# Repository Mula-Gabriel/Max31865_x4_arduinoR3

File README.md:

Fichier format kicad v6.
Shield pour 4 sondes pt100 3/4 fils, format arduino, avec 4 max31865.

# Max31865_x4_arduinoR3   
Exemple code https://github.com/Mula-Gabriel/Max31865_x4_arduinoR3_STM32

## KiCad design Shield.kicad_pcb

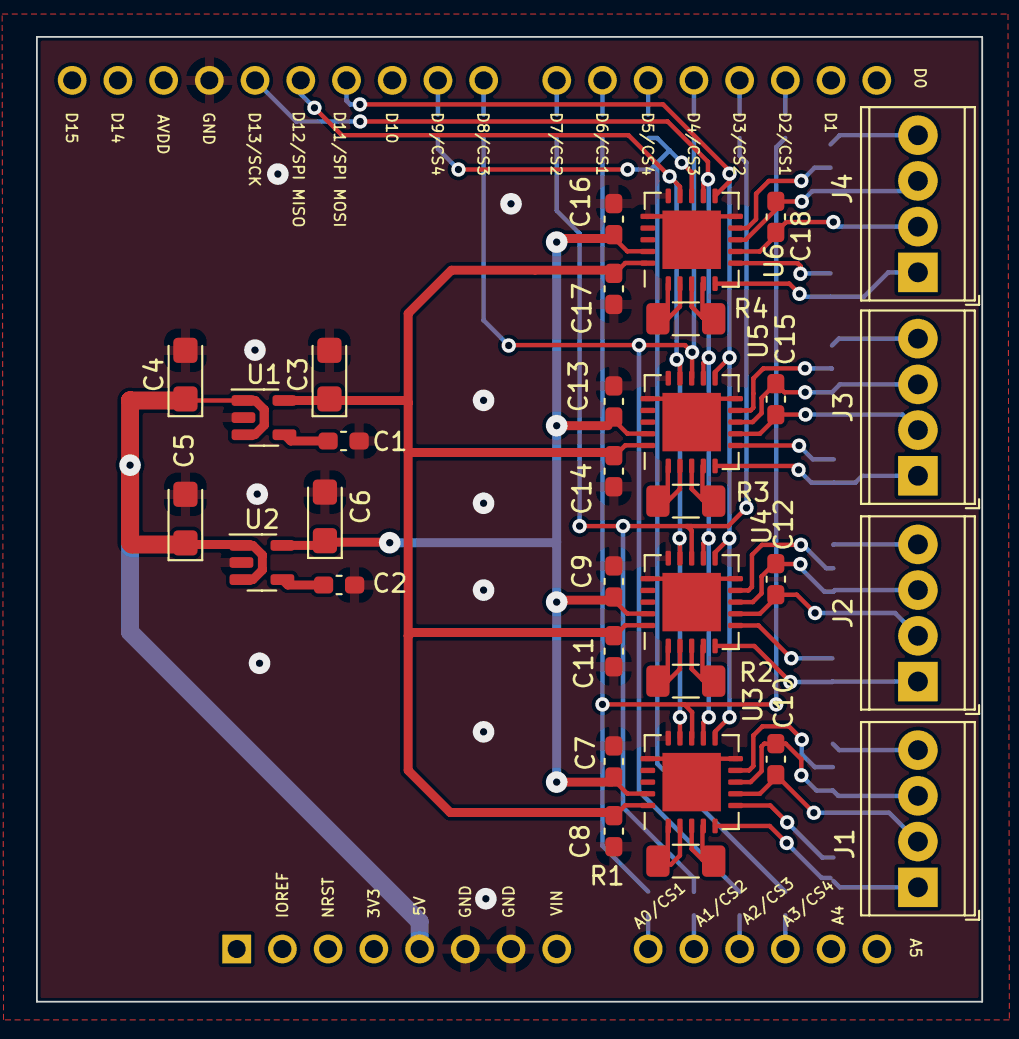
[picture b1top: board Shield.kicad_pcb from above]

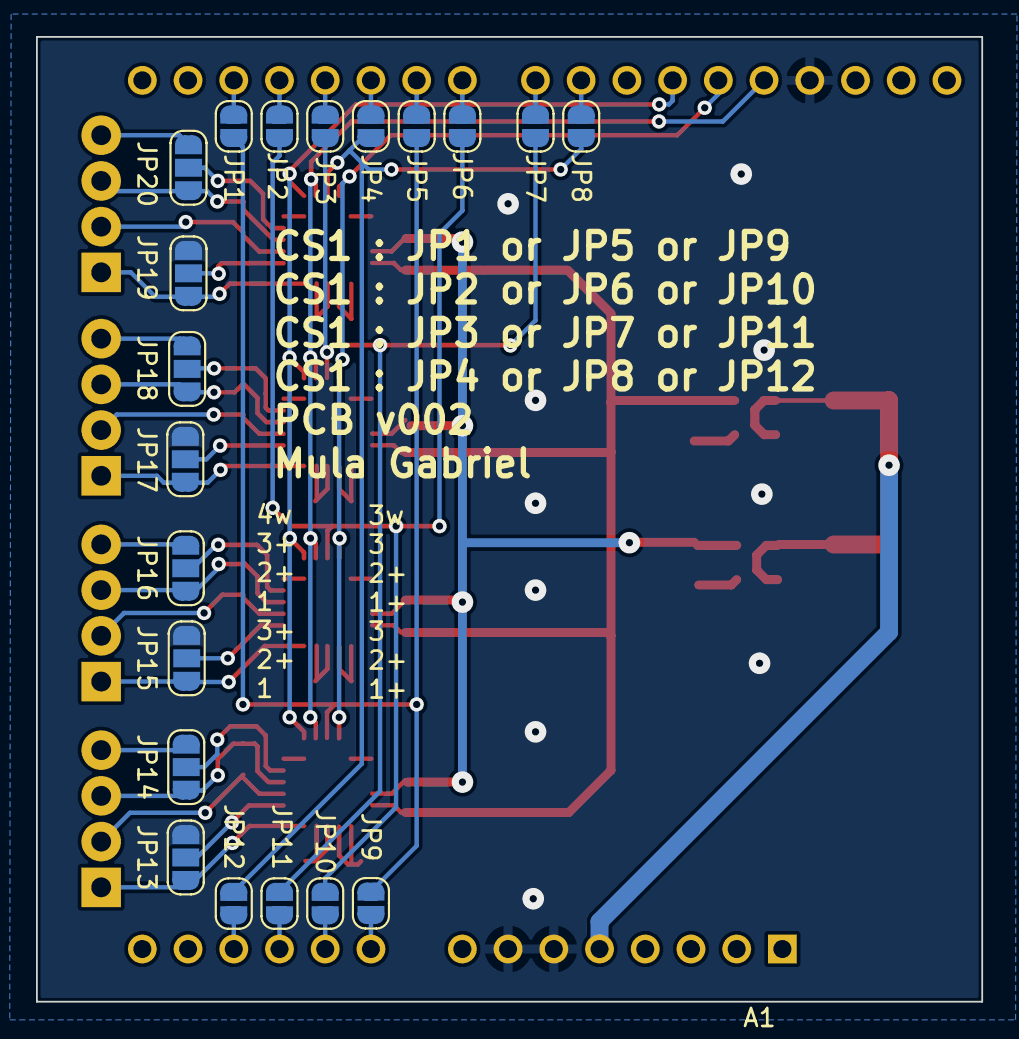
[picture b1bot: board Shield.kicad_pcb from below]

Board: 2 copper layers, 52.5 x 53.6 mm, 53 parts (21 on the bottom side), 57 nets.

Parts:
A1: Arduino_UNO_R3; Arduino_UNO_R3_3d
C1, C2: 100 nF; C_0603_1608Metric_Pad1.08x0.95mm_HandSolder
C3, C6: 10uF; CP_EIA-3216-18_Kemet-A
C4, C5: 1uF; CP_EIA-3216-18_Kemet-A
C7, C8, C9, C10, C11, C12, C13, C14, C15, C16, C17, C18: 100nF; C_0603_1608Metric_Pad1.08x0.95mm_HandSolder
J1, J2, J3, J4: Screw_Terminal_01x04; TerminalBlock_Phoenix_MPT-0,5-4-2.54_1x04_P2.54mm_Horizontal
JP1, JP2, JP3, JP4, JP5, JP6, JP7, JP8: SolderJumper_2_Open; SolderJumper-2_P1.3mm_Open_RoundedPad1.0x1.5mm
JP9, JP10, JP11, JP12: SolderJumper_2_Bridged; SolderJumper-2_P1.3mm_Open_RoundedPad1.0x1.5mm
JP13, JP14, JP15, JP16, JP17, JP18, JP19, JP20: SolderJumper_3_Open; SolderJumper-3_P1.3mm_Open_RoundedPad1.0x1.5mm_NumberLabels
R1, R2, R3, R4: 400 0.1%; R_1206_3216Metric_Pad1.30x1.75mm_HandSolder
U1, U2: SPX3819M5-L-3-3; SOT-23-5
U3, U4, U5, U6: MAX31865xTP; TQFN-20-1EP_5x5mm_P0.65mm_EP3.25x3.25mm

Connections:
+3.3V: C6.1, C7.2, C9.2, C13.2, C16.2, U2.5 (OUT), U3.19 (DVDD), U4.19 (DVDD), U5.19 (DVDD), U6.19 (DVDD)
+3.3VA: C3.1, C8.1, C11.1, C14.1, C17.1, U1.5 (OUT), U3.20 (VDD), U4.20 (VDD), U5.20 (VDD), U6.20 (VDD)
+5V: A1.5 (+5V), C4.1, C5.1, U1.1 (IN), U1.3 (EN), U2.1 (IN), U2.3 (EN)
/CS_MAX1: JP1.1 (A), JP5.1 (A), JP9.2 (B), U3.13 (~CS)
/CS_MAX2: JP2.1 (A), JP6.1 (A), JP10.2 (B), U4.13 (~CS)
/CS_MAX3: JP3.1 (A), JP7.1 (A), JP11.2 (B), U5.13 (~CS)
/CS_MAX4: JP4.1 (A), JP8.1 (A), JP12.2 (B), U6.13 (~CS)
/SPI2_MISO: A1.27 (D12), U3.14 (SDO), U4.14 (SDO), U5.14 (SDO), U6.14 (SDO)
/SPI2_MOSI: A1.26 (D11), U3.11 (SDI), U4.11 (SDI), U5.11 (SDI), U6.11 (SDI)
/SPI2_SCK: A1.28 (D13), U3.12 (SCLK), U4.12 (SCLK), U5.12 (SCLK), U6.12 (SCLK)
GND: A1.6 (GND), A1.7 (GND), A1.29 (GND), C1.2, C2.2, C3.2, C4.2, C5.2, C6.2, C7.1, C8.2, C9.1, C11.2, C13.1, C14.2, C16.1, C17.2, JP13.3 (B), JP15.3 (B), JP17.3 (B), JP19.3 (B), U1.2 (GND), U2.2 (GND), U3.10 (GND), U3.15 (DGND), U3.16 (GND), U3.21 (GND), U4.10 (GND), U4.15 (DGND), U4.16 (GND), U4.21 (GND), U5.10 (GND), U5.15 (DGND), U5.16 (GND), U5.21 (GND), U6.10 (GND), U6.15 (DGND), U6.16 (GND), U6.21 (GND)
unnamed: A1.9 (A0), JP9.1 (A)
unnamed: A1.10 (A1), JP10.1 (A)
unnamed: A1.11 (A2), JP11.1 (A)
unnamed: A1.12 (A3), JP12.1 (A)
unnamed: A1.17 (D2), JP1.2 (B)
unnamed: A1.18 (D3), JP2.2 (B)
unnamed: A1.19 (D4), JP3.2 (B)
unnamed: A1.20 (D5), JP4.2 (B)
unnamed: A1.21 (D6), JP5.2 (B)
unnamed: A1.22 (D7), JP6.2 (B)
unnamed: A1.23 (D8), JP7.2 (B)
unnamed: A1.24 (D9), JP8.2 (B)
unnamed: C1.1, U1.4 (BP)
unnamed: C2.1, U2.4 (BP)
unnamed: C10.1, J1.3, JP14.1 (A), U3.8 (RTDIN-)
unnamed: C10.2, J1.2, U3.7 (RTDIN+)
unnamed: C12.1, J2.3, JP16.1 (A), U4.8 (RTDIN-)
unnamed: C12.2, J2.2, U4.7 (RTDIN+)
unnamed: C15.1, J3.3, JP18.1 (A), U5.8 (RTDIN-)
unnamed: C15.2, J3.2, U5.7 (RTDIN+)
unnamed: C18.1, J4.3, JP20.1 (A), U6.8 (RTDIN-)
unnamed: C18.2, J4.2, U6.7 (RTDIN+)
unnamed: J1.1, JP13.1 (A), U3.5 (FORCE+)
unnamed: J1.4, JP14.3 (B)
unnamed: J2.1, JP15.1 (A), U4.5 (FORCE+)
unnamed: J2.4, JP16.3 (B)
unnamed: J3.1, JP17.1 (A), U5.5 (FORCE+)
unnamed: J3.4, JP18.3 (B)
unnamed: J4.1, JP19.1 (A), U6.5 (FORCE+)
unnamed: J4.4, JP20.3 (B)
unnamed: JP13.2 (C), U3.6 (FORCE2)
unnamed: JP14.2 (C), U3.9 (FORCE-)
unnamed: JP15.2 (C), U4.6 (FORCE2)
unnamed: JP16.2 (C), U4.9 (FORCE-)
unnamed: JP17.2 (C), U5.6 (FORCE2)
unnamed: JP18.2 (C), U5.9 (FORCE-)
unnamed: JP19.2 (C), U6.6 (FORCE2)
unnamed: JP20.2 (C), U6.9 (FORCE-)
unnamed: R1.1, U3.1 (BIAS), U3.2 (REFIN+)
unnamed: R1.2, U3.3 (REFIN-), U3.4 (ISENSOR)
unnamed: R2.1, U4.1 (BIAS), U4.2 (REFIN+)
unnamed: R2.2, U4.3 (REFIN-), U4.4 (ISENSOR)
unnamed: R3.1, U5.1 (BIAS), U5.2 (REFIN+)
unnamed: R3.2, U5.3 (REFIN-), U5.4 (ISENSOR)
unnamed: R4.1, U6.1 (BIAS), U6.2 (REFIN+)
unnamed: R4.2, U6.3 (REFIN-), U6.4 (ISENSOR)

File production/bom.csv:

Designator,Footprint,Quantity,Value,LCSC Part #
A1,Arduino_UNO_R3_3d,1,Arduino_UNO_R3,
"C1, C2",C_0603_1608Metric_Pad1.08x0.95mm_HandSolder,2,100 nF,
"C10, C11, C12, C13, C14, C15, C16, C17, C18, C7, C8, C9",C_0603_1608Metric_Pad1.08x0.95mm_HandSolder,12,100nF,
"C3, C6",CP_EIA-3216-18_Kemet-A,2,10uF,
"C4, C5",CP_EIA-3216-18_Kemet-A,2,1uF,
"J1, J2, J3, J4","TerminalBlock_Phoenix_MPT-0,5-4-2.54_1x04_P2.54mm_Horizontal",4,Screw_Terminal_01x04,
"JP1, JP2, JP3, JP4, JP5, JP6, JP7, JP8",SolderJumper-2_P1.3mm_Open_RoundedPad1.0x1.5mm,8,SolderJumper_2_Open,
"JP10, JP11, JP12, JP9",SolderJumper-2_P1.3mm_Open_RoundedPad1.0x1.5mm,4,SolderJumper_2_Bridged,
"JP13, JP14, JP15, JP16, JP17, JP18, JP19, JP20",SolderJumper-3_P1.3mm_Open_RoundedPad1.0x1.5mm_NumberLabels,8,SolderJumper_3_Open,
"R1, R2, R3, R4",R_1206_3216Metric_Pad1.30x1.75mm_HandSolder,4,400 0.1%,
"U1, U2",SOT-23-5,2,SPX3819M5-L-3-3,
"U3, U4, U5, U6",TQFN-20-1EP_5x5mm_P0.65mm_EP3.25x3.25mm,4,MAX31865xTP,

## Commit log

2022-11-19 git ignore
2022-11-19 Supprime le contour arduino qui fait plein d'erreur DRC
2022-11-19 0 DRC
2022-11-20 Passe l'empreinte en TSOP
2022-11-21 Passe certaine empreinte en 0603
2022-11-21 Passe les resistance 400 ohm en 1206
2022-11-21 Change le regulateur, le microchip est dur a avoir
2023-02-10 v002
    AJoute des grains de café pour choisir le chip select
    Miroir connecteur arduiono
2023-02-10 Ajoute img et update connecteur avec 3d
2023-02-13 Ajoute selection 4w/3w Ajoute marquage v002
